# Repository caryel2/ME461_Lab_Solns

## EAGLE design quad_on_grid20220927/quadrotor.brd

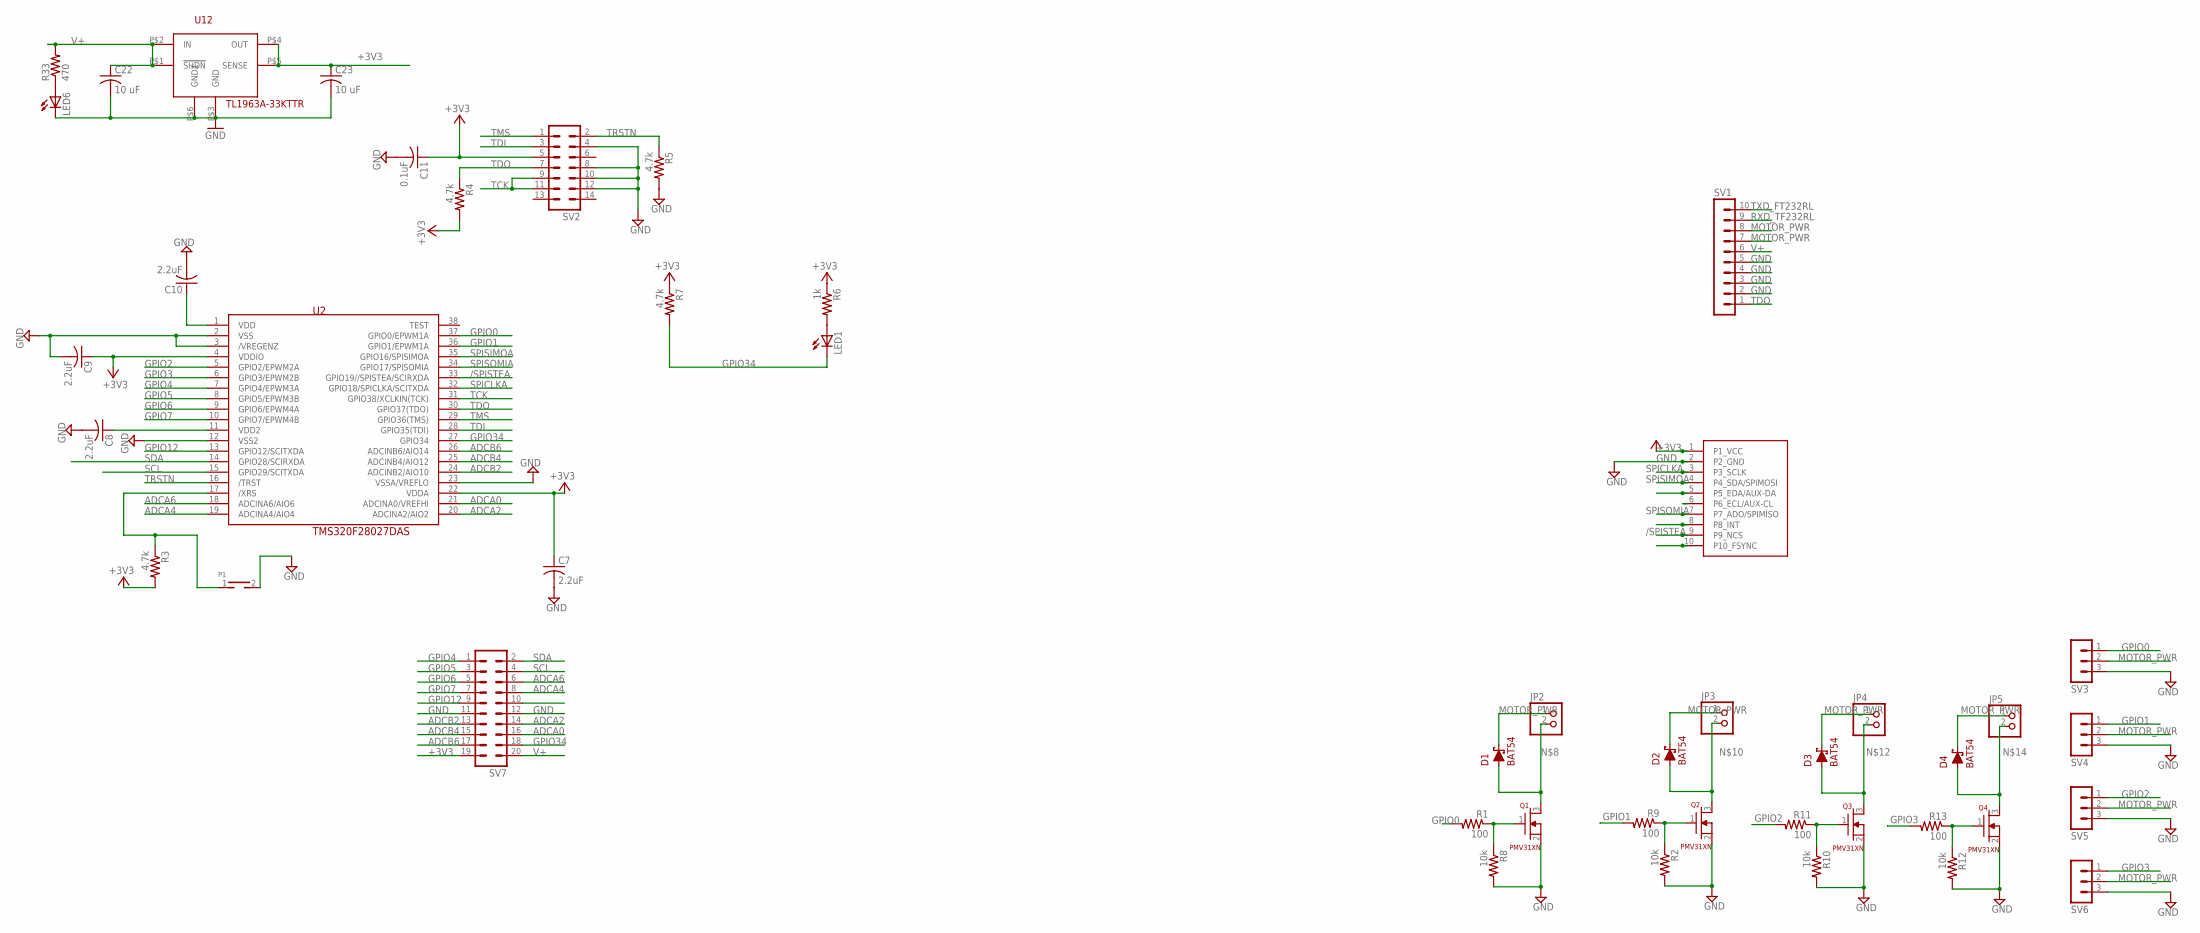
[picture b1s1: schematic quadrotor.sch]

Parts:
C7, C8, C9, C10: 2.2uF; C1206
C11: 0.1uF; C1206
C22, C23: 10 uF; C1206
D1, D2, D3, D4: BAT54; SOT23
JP2, JP3, JP4, JP5: PINHD-1X2; 1X02
LED1, LED6: LEDCHIPLED_1206; CHIPLED_1206
P1: TH_PUSHBOTTON; TH_PUSHBUTTON
Q1, Q2, Q3, Q4: PMV31XN; SOT23
R1, R9, R11, R13: 100; R1206
R2, R8, R10, R12: 10k; R1206
R3, R4, R5, R7: 4.7k; R1206
R6: 1k; R1206
R33: 470; M1206
SV1: MA10-1
SV2: MA07-2
SV3, SV4, SV5, SV6: MA03-1
SV7: MA10-2
U2: TMS320F28027DAS; DA38
U12: TL1963A-33KTTR; TL1963AKTTR
U$1: MPU-9250-BB

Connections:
+3V3: C7.1, C9.1, C11.1, C23.1, R3.2, R4.2, R6.1, R7.1, SV2.5, SV7.19, U2.4 (VDDIO), U2.22 (VDDA), U12.P$4 (OUT), U12.P$5 (SENSE), U$1.1 (P1_VCC)
/SPISTEA: U2.33 (GPIO19//SPISTEA/SCIRXDA), U$1.9 (P9_NCS)
ADCA0: SV7.16, U2.21 (ADCINA0/VREFHI)
ADCA2: SV7.14, U2.20 (ADCINA2/AIO2)
ADCA4: SV7.8, U2.19 (ADCINA4/AIO4)
ADCA6: SV7.6, U2.18 (ADCINA6/AIO6)
ADCB2: SV7.13, U2.24 (ADCINB2/AIO10)
ADCB4: SV7.15, U2.25 (ADCINB4/AIO12)
ADCB6: SV7.17, U2.26 (ADCINB6/AIO14)
ASCL: U$1.6 (P6_ECL/AUX-CL)
ASDA: U$1.5 (P5_EDA/AUX-DA)
FSYNC: U$1.10 (P10_FSYNC)
GND: C7.2, C8.2, C9.2, C10.2, C11.2, C22.2, C23.2, LED6.C, P1.2, Q1.2 (S), Q2.2 (S), Q3.2 (S), Q4.2 (S), R2.2, R5.2, R8.2, R10.2, R12.2, SV1.2, SV1.3, SV1.4, SV1.5, SV2.4, SV2.8, SV2.10, SV2.12, SV3.3, SV4.3, SV5.3, SV6.3, SV7.11, SV7.12, U2.2 (VSS), U2.3 (/VREGENZ), U2.12 (VSS2), U2.23 (VSSA/VREFLO), U12.P$3 (GND), U12.P$6 (GND1), U$1.2 (P2_GND)
GPIO0: R1.2, SV3.1, U2.37 (GPIO0/EPWM1A)
GPIO1: R9.2, SV4.1, U2.36 (GPIO1/EPWM1A)
GPIO2: R11.2, SV5.1, U2.5 (GPIO2/EPWM2A)
GPIO3: R13.2, SV6.1, U2.6 (GPIO3/EPWM2B)
GPIO4: SV7.1, U2.7 (GPIO4/EPWM3A)
GPIO5: SV7.3, U2.8 (GPIO5/EPWM3B)
GPIO6: SV7.5, U2.9 (GPIO6/EPWM4A)
GPIO7: SV7.7, U2.10 (GPIO7/EPWM4B)
GPIO12: SV7.9, U2.13 (GPIO12/SCITXDA)
GPIO34: LED1.C, R7.2, SV7.18, U2.27 (GPIO34)
INT: U$1.8 (P8_INT)
MOTOR_PWR: D1.3, D2.3, D3.3, D4.3, JP2.1, JP3.1, JP4.1, JP5.1, SV1.7, SV1.8, SV3.2, SV4.2, SV5.2, SV6.2
unnamed: LED1.A, R6.2
unnamed: Q1.1 (G), R1.1, R8.1
unnamed: C8.1, U2.11 (VDD2)
unnamed: Q3.1 (G), R10.1, R11.1
unnamed: Q2.1 (G), R2.1, R9.1
unnamed: Q4.1 (G), R12.1, R13.1
unnamed: D1.1, JP2.2, Q1.3 (D)
unnamed: D2.1, JP3.2, Q2.3 (D)
unnamed: D3.1, JP4.2, Q3.3 (D)
unnamed: D4.1, JP5.2, Q4.3 (D)
unnamed: C10.1, U2.1 (VDD)
unnamed: P1.1, R3.1, U2.17 (/XRS)
unnamed: LED6.A, R33.1
RXD_TF232RL: SV1.9
SCL: SV7.4, U2.15 (GPIO29/SCITXDA)
SDA: SV7.2, U2.14 (GPIO28/SCIRXDA)
SPICLKA: U2.32 (GPIO18/SPICLKA/SCITXDA), U$1.3 (P3_SCLK)
SPISIMOA: U2.35 (GPIO16/SPISIMOA), U$1.4 (P4_SDA/SPIMOSI)
SPISOMIA: U2.34 (GPIO17/SPISOMIA), U$1.7 (P7_ADO/SPIMISO)
TCK: SV2.9, SV2.11, U2.31 (GPIO38/XCLKIN(TCK))
TDI: SV2.3, U2.28 (GPIO35(TDI))
TDO: R4.1, SV1.1, SV2.7, U2.30 (GPIO37(TDO))
TMS: SV2.1, U2.29 (GPIO36(TMS))
TRSTN: R5.1, SV2.2, U2.16 (/TRST)
TXD_FT232RL: SV1.10
V+: C22.1, R33.2, SV1.6, SV7.20, U12.P$1 (!SHDN), U12.P$2 (IN)

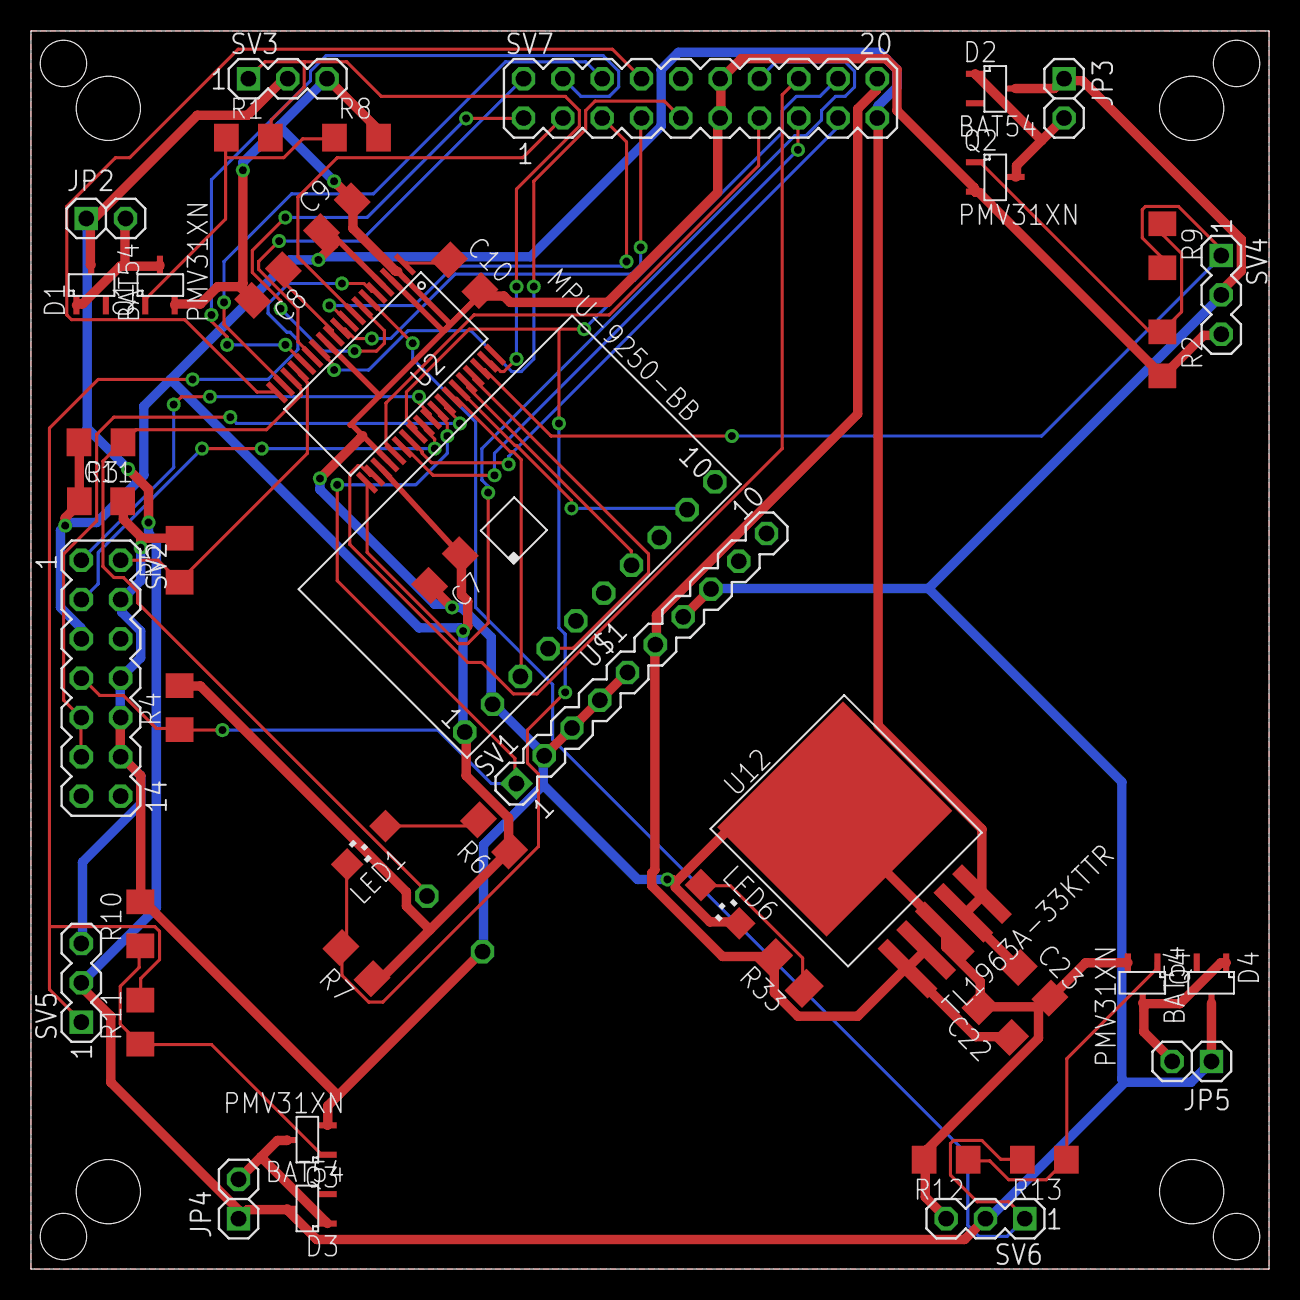
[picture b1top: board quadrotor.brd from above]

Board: 2 copper layers, 80.0 x 80.0 mm, 46 parts (1 on the bottom side), 45 nets.

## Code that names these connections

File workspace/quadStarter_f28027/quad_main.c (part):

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

    EALLOW;
    GpioCtrlRegs.GPAPUD.bit.GPIO0 = 1;    // Disable pull-up on GPIO0 (EPWM1A)
    GpioCtrlRegs.GPAMUX1.bit.GPIO0 = 1;   // Configure GPIO0 as EPWM1A

    GpioCtrlRegs.GPAPUD.bit.GPIO1 = 1;    // Disable pull-up on GPIO1 (EPWM1B)
    GpioCtrlRegs.GPAMUX1.bit.GPIO1 = 1;   // Configure GPIO1 as EPWM1B

    GpioCtrlRegs.GPAPUD.bit.GPIO2 = 1;    // Disable pull-up on GPIO2 (EPWM2A)
    GpioCtrlRegs.GPAMUX1.bit.GPIO2 = 1;   // Configure GPIO2 as EPWM2A

    GpioCtrlRegs.GPAPUD.bit.GPIO3 = 1;    // Disable pull-up on GPIO3 (EPWM2B)
    GpioCtrlRegs.GPAMUX1.bit.GPIO3 = 1;   // Configure GPIO3 as EPWM2B
    EDIS;

    EPwm1Regs.TBCTL.bit.CTRMODE = 0;      //set epwm2 to upcount mode
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    PieCtrlRegs.PIEIER1.bit.INTx7 = 1;

    EALLOW;
    GpioCtrlRegs.GPBMUX1.bit.GPIO34 = 0;
    GpioDataRegs.GPBCLEAR.bit.GPIO34 = 1;
    GpioCtrlRegs.GPBDIR.bit.GPIO34 = 1;
    GpioCtrlRegs.GPBPUD.bit.GPIO34 = 1;

    GpioCtrlRegs.GPAPUD.bit.GPIO5 = 1;    // Disable pull-up on GPIO5 (EPWM3B)
    GpioCtrlRegs.GPAMUX1.bit.GPIO5 = 0;   // Configure GPIO5 as EPWM3B
    GpioCtrlRegs.GPADIR.bit.GPIO5 = 1;
    GpioDataRegs.GPACLEAR.bit.GPIO5 = 1;
    EDIS;

    SpiaRegs.SPIFFRX.bit.RXFFOVFCLR=1;  // Clear Overflow flag
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__interrupt void adc_isr(void)
{

    GpioDataRegs.GPASET.bit.GPIO5 = 1;
    ADC0raw = AdcResult.ADCRESULT0;
    ADC2raw = AdcResult.ADCRESULT1;

    ADCcount++;
    if ((ADCcount%50)==0) {
        GpioDataRegs.GPBTOGGLE.bit.GPIO34 = 1;
    }

    if (SPI_Interrupt_Finished == 1) {
        SPI_Interrupt_Finished = 0;
        SpiaRegs.SPIFFRX.bit.RXFFIL = 4;

        GpioDataRegs.GPACLEAR.bit.GPIO19 = 1;

        SpiaRegs.SPITXBUF = ((0x8000)|(0x3A00));
        SpiaRegs.SPITXBUF = 0;
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    if (Timer0Count > 32000) { // Rolls over at 32767 so catch before that point
        Timer0Count = 0;
    }
   // GpioDataRegs.GPBTOGGLE.bit.GPIO34 = 1;
    UARTPrint = 1;
    //
    // Acknowledge this interrupt to receive more interrupts from group 1
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}

void SPI_RXint(void) {
//    GpioDataRegs.GPASET.bit.GPIO5 = 1;
    uint16_t i;

    switch (SPIenc_state) {
    case 4:
        GpioDataRegs.GPASET.bit.GPIO19 = 1;                 //Pull CS high as done R/W
        for (i=0; i<4; i++) {
            readdata[i] = SpiaRegs.SPIRXBUF; // readdata[0] is garbage
        }
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

        SpiaRegs.SPIFFRX.bit.RXFFIL = 4;
        GpioDataRegs.GPACLEAR.bit.GPIO19 = 1;

        SpiaRegs.SPITXBUF = ((0x8000)|(0x4200));
        SpiaRegs.SPITXBUF = 0;
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        SPIenc_state = 5;
        break;
    case 5:
        GpioDataRegs.GPASET.bit.GPIO19 = 1;                 //Pull CS high as done R/W
        for (i=0; i<4; i++) {
            readdata[i] = SpiaRegs.SPIRXBUF; // readdata[0] is garbage
        }
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        gyroz  = gyroZraw*250.0/32767.0;

        SpiaRegs.SPIFFRX.bit.RXFFIL = 4;
        GpioDataRegs.GPACLEAR.bit.GPIO19 = 1;

        SpiaRegs.SPITXBUF = ((0x8000)|(0x4A00));
        SpiaRegs.SPITXBUF = 0;
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
        break;
    case 6:
        GpioDataRegs.GPASET.bit.GPIO19 = 1;                 //Pull CS high as done R/W
        for (i=0; i<4; i++) {
            readdata[i] = SpiaRegs.SPIRXBUF; // readdata[0] is garbage
        }
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
        }
        SPI_Interrupt_Finished = 1;
        GpioDataRegs.GPACLEAR.bit.GPIO5 = 1;
        break;

    }
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void setupSpia(void)        //for mpu9250
{
    EALLOW;
    GpioCtrlRegs.GPAPUD.bit.GPIO16 = 0;    // Enable pull-up on GPIO16 (SIMO)
    GpioCtrlRegs.GPAMUX2.bit.GPIO16 = 1;   // Configure GPIO16 as SIMO

    GpioCtrlRegs.GPAPUD.bit.GPIO17 = 0;    // Enable pull-up on GPIO17 (SOMI)
    GpioCtrlRegs.GPAMUX2.bit.GPIO17 = 1;   // Configure GPIO17 as SOMI

    GpioCtrlRegs.GPAPUD.bit.GPIO18 = 0;    // Enable pull-up on GPIO18 (CLK)
    GpioCtrlRegs.GPAMUX2.bit.GPIO18 = 1;   // Configure GPIO18 as CLK

    GpioCtrlRegs.GPAMUX2.bit.GPIO19 = 0;
    GpioDataRegs.GPASET.bit.GPIO19 = 1;
    GpioCtrlRegs.GPADIR.bit.GPIO19 = 1;
    GpioCtrlRegs.GPAPUD.bit.GPIO19 = 1;

    EDIS;

    EALLOW;
    GpioCtrlRegs.GPAQSEL2.bit.GPIO16 = 3; // Set I/O pin to asynchronous mode recommended for SPI
    GpioCtrlRegs.GPAQSEL2.bit.GPIO17 = 3; // Set I/O pin to asynchronous mode recommended for SPI
    GpioCtrlRegs.GPAQSEL2.bit.GPIO18 = 3; // Set I/O pin to asynchronous mode recommended for SPI
    EDIS;

    SpiaRegs.SPICCR.bit.SPISWRESET   = 0;    // Put SPI in Reset
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
    //-----------------------------------------------------------------------------------------------------------------

    GpioDataRegs.GPACLEAR.bit.GPIO19 = 1;
    SpiaRegs.SPITXBUF = (0x1300         | 0x00); // 0x1300 (0x0000)
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
    while(SpiaRegs.SPIFFRX.bit.RXFFST !=4);
    GpioDataRegs.GPASET.bit.GPIO19 = 1;
    temp = SpiaRegs.SPIRXBUF;
    temp = SpiaRegs.SPIRXBUF;
    temp = SpiaRegs.SPIRXBUF;
    temp = SpiaRegs.SPIRXBUF;

    DELAY_US(10);
    GpioDataRegs.GPACLEAR.bit.GPIO19 = 1;
    SpiaRegs.SPITXBUF = (0x1A00         | 0x02); //0x1A00 (0x0002),

    while(SpiaRegs.SPIFFRX.bit.RXFFST !=1);
    GpioDataRegs.GPASET.bit.GPIO19 = 1;
    temp = SpiaRegs.SPIRXBUF;

    DELAY_US(10);
    GpioDataRegs.GPACLEAR.bit.GPIO19 = 1;
    SpiaRegs.SPITXBUF = (0x1B00         | 0x00); // 0x1B00 (0x0000), 250 dps
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
    while(SpiaRegs.SPIFFRX.bit.RXFFST !=3);
    GpioDataRegs.GPASET.bit.GPIO19 = 1;
    temp = SpiaRegs.SPIRXBUF;
    temp = SpiaRegs.SPIRXBUF;
    temp = SpiaRegs.SPIRXBUF;

    DELAY_US(10);

    GpioDataRegs.GPACLEAR.bit.GPIO19 = 1;
    SpiaRegs.SPITXBUF = (FIFO_EN        | 0x0000); // 0x2300 (0x0000)
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    while(SpiaRegs.SPIFFRX.bit.RXFFST !=4);
    GpioDataRegs.GPASET.bit.GPIO19 = 1;
    temp = SpiaRegs.SPIRXBUF;
    temp = SpiaRegs.SPIRXBUF;
    temp = SpiaRegs.SPIRXBUF;
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
    DELAY_US(10);

    GpioDataRegs.GPACLEAR.bit.GPIO19 = 1;
    SpiaRegs.SPITXBUF = (I2C_SLV1_CTRL | 0x0081);  // 0x2A00 (0x0081)
    while(SpiaRegs.SPIFFRX.bit.RXFFST !=1);
    GpioDataRegs.GPASET.bit.GPIO19 = 1;
    temp = SpiaRegs.SPIRXBUF;

    DELAY_US(10);

    GpioDataRegs.GPACLEAR.bit.GPIO19 = 1;
    SpiaRegs.SPITXBUF = (INT_ENABLE | 0x0001);  // 0x3800
    while(SpiaRegs.SPIFFRX.bit.RXFFST !=1);
    GpioDataRegs.GPASET.bit.GPIO19 = 1;
    temp = SpiaRegs.SPIRXBUF;

    DELAY_US(10);

    GpioDataRegs.GPACLEAR.bit.GPIO19 = 1;
    SpiaRegs.SPITXBUF = (INT_STATUS | 0x0001);  // 0x3A00
    while(SpiaRegs.SPIFFRX.bit.RXFFST !=1);
    GpioDataRegs.GPASET.bit.GPIO19 = 1;
    temp = SpiaRegs.SPIRXBUF;

    DELAY_US(10);

    GpioDataRegs.GPACLEAR.bit.GPIO19 = 1;
    SpiaRegs.SPITXBUF = (I2C_SLV1_DO | 0x0001);  // 0x6400
    while(SpiaRegs.SPIFFRX.bit.RXFFST !=1);
    GpioDataRegs.GPASET.bit.GPIO19 = 1;
    temp = SpiaRegs.SPIRXBUF;

    DELAY_US(10);

    GpioDataRegs.GPACLEAR.bit.GPIO19 = 1;
    SpiaRegs.SPITXBUF = (I2C_MST_DELAY_CTRL | 0x0003); // 0x6700
    while(SpiaRegs.SPIFFRX.bit.RXFFST !=1);
    GpioDataRegs.GPASET.bit.GPIO19 = 1;
    temp = SpiaRegs.SPIRXBUF;

    DELAY_US(10);

    GpioDataRegs.GPACLEAR.bit.GPIO19 = 1;
    SpiaRegs.SPITXBUF = (USER_CTRL | 0x0020);  // 0x6A00
    while(SpiaRegs.SPIFFRX.bit.RXFFST !=1);
    GpioDataRegs.GPASET.bit.GPIO19 = 1;
    temp = SpiaRegs.SPIRXBUF;

    DELAY_US(10);

    GpioDataRegs.GPACLEAR.bit.GPIO19 = 1;
    SpiaRegs.SPITXBUF = (PWR_MGMT_1 | 0x0001); // 0x6B00
    while(SpiaRegs.SPIFFRX.bit.RXFFST !=1);
    GpioDataRegs.GPASET.bit.GPIO19 = 1;
    temp = SpiaRegs.SPIRXBUF;

    DELAY_US(10);

    GpioDataRegs.GPACLEAR.bit.GPIO19 = 1;
    SpiaRegs.SPITXBUF = (WHO_AM_I | 0x0071);  // 0x7500
    while(SpiaRegs.SPIFFRX.bit.RXFFST !=1);
    GpioDataRegs.GPASET.bit.GPIO19 = 1;
    temp = SpiaRegs.SPIRXBUF;

    DELAY_US(10);

    GpioDataRegs.GPACLEAR.bit.GPIO19 = 1;
    SpiaRegs.SPITXBUF = (XA_OFFSET_H | 0x00EB); // 0x7700
    while(SpiaRegs.SPIFFRX.bit.RXFFST !=1);
    GpioDataRegs.GPASET.bit.GPIO19 = 1;
    temp = SpiaRegs.SPIRXBUF;

    DELAY_US(10);

    GpioDataRegs.GPACLEAR.bit.GPIO19 = 1;
    SpiaRegs.SPITXBUF = (XA_OFFSET_L | 0x0012); // 0x7800
    while(SpiaRegs.SPIFFRX.bit.RXFFST !=1);
    GpioDataRegs.GPASET.bit.GPIO19 = 1;
    temp = SpiaRegs.SPIRXBUF;

    DELAY_US(10);

    GpioDataRegs.GPACLEAR.bit.GPIO19 = 1;
    SpiaRegs.SPITXBUF = (YA_OFFSET_H | 0x0018); // 0x7A00
    while(SpiaRegs.SPIFFRX.bit.RXFFST !=1);
    GpioDataRegs.GPASET.bit.GPIO19 = 1;
    temp = SpiaRegs.SPIRXBUF;

    DELAY_US(10);

    GpioDataRegs.GPACLEAR.bit.GPIO19 = 1;
    SpiaRegs.SPITXBUF = (YA_OFFSET_L | 0x0000); // 0x7B00
    while(SpiaRegs.SPIFFRX.bit.RXFFST !=1);
    GpioDataRegs.GPASET.bit.GPIO19 = 1;
    temp = SpiaRegs.SPIRXBUF;

    DELAY_US(10);

    GpioDataRegs.GPACLEAR.bit.GPIO19 = 1;
    SpiaRegs.SPITXBUF = (ZA_OFFSET_H | 0x0021); // 0x7D00
    while(SpiaRegs.SPIFFRX.bit.RXFFST !=1);
    GpioDataRegs.GPASET.bit.GPIO19 = 1;
    temp = SpiaRegs.SPIRXBUF;

    DELAY_US(10);

    GpioDataRegs.GPACLEAR.bit.GPIO19 = 1;
    SpiaRegs.SPITXBUF = (ZA_OFFSET_L | 0x0050); // 0x7E00
    while(SpiaRegs.SPIFFRX.bit.RXFFST !=1);
    GpioDataRegs.GPASET.bit.GPIO19 = 1;
    temp = SpiaRegs.SPIRXBUF;

    while(SpiaRegs.SPIFFRX.bit.RXFFST !=0){
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
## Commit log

2023-01-10 Commited work done during Fall 22 Semester
2023-02-19 Added Diego's Group final code
2023-05-30 Lab 1 done
2023-06-01 Lab 2 done, Lab 3 started
2023-06-16 Lab 4 DONE
2023-07-10 Lab 6 almost done
2023-07-19 Lab 6 done, lab 7 start
2023-07-24 Blah
2023-09-13 Lab 3 first commit
